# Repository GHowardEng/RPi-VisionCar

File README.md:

# RPi-VisionCar
## OpenCV vision-based maze car project

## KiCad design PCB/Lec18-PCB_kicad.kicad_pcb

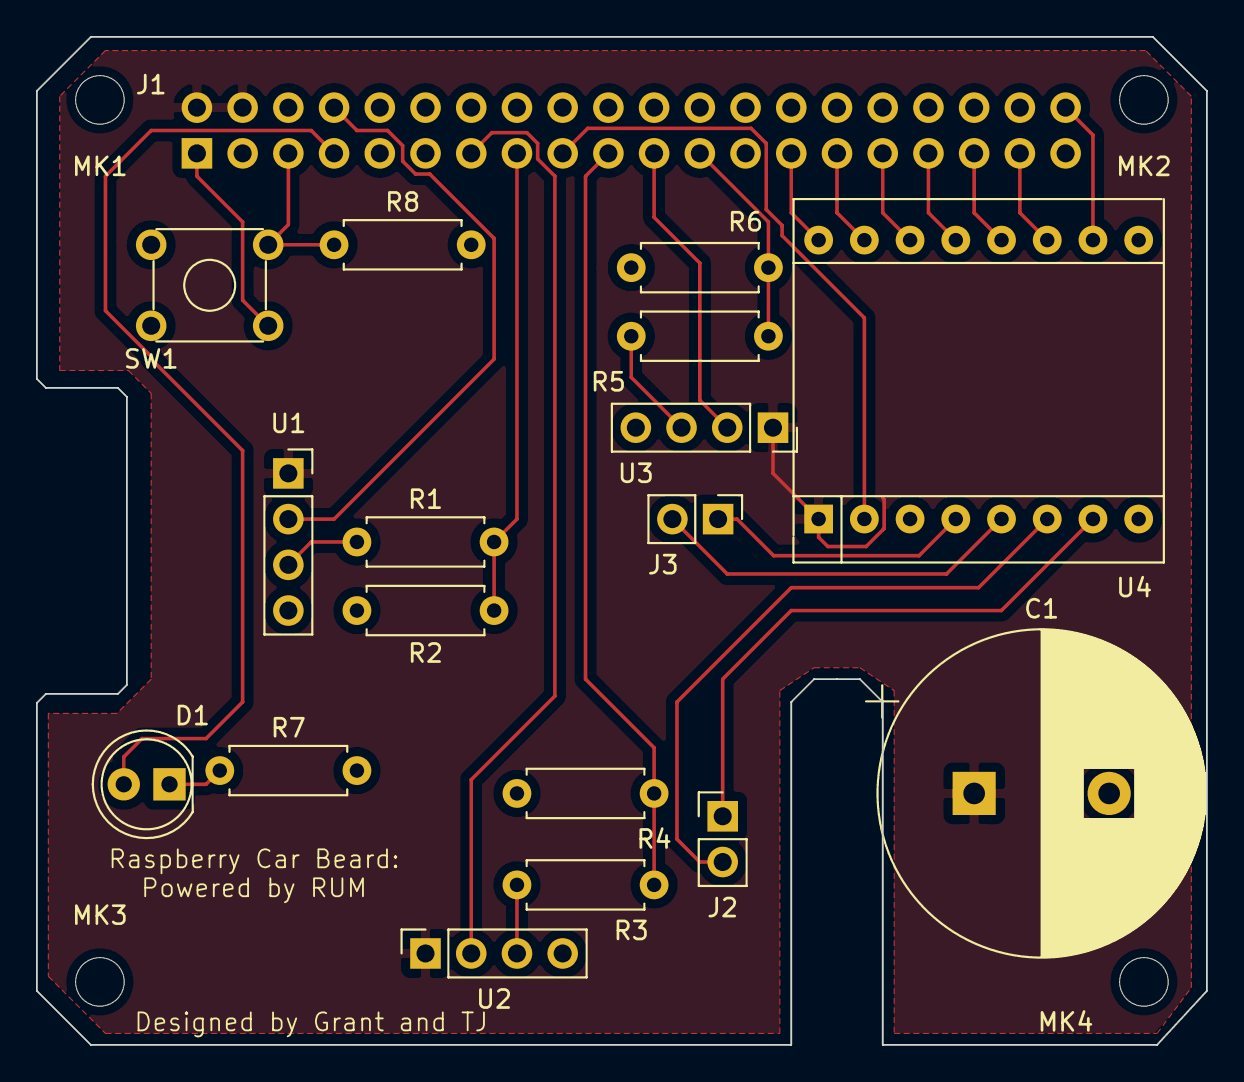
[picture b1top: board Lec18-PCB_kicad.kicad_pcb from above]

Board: 2 copper layers, 65.0 x 56.0 mm, 22 parts (1 on the bottom side), 26 nets.

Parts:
C1: CAP; CP_Radial_D18.0mm_P7.50mm
D1: LED; LED_D5.0mm
J1: Raspberry_Pi_2_3; PinSocket_2x20_P2.54mm_Vertical
J2, J3: Conn_01x02_Male; PinHeader_1x02_P2.54mm_Vertical
MK1, MK2, MK3, MK4: M2.5; MountingHole_2.7mm_M2.5
R1, R2, R3, R4, R5, R6, R7, R8: R; R_Axial_DIN0207_L6.3mm_D2.5mm_P7.62mm_Horizontal
SW1: SW_Push_Dual; SW_TH_Tactile_Omron_B3F-10xx
U1, U2, U3: HC-SR04; PinSocket_1x04_P2.54mm_Vertical
U4: TB6612FNG_BREAKOUT; SparkFun_TB6612_foot

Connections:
+3V3: J1.1, J1.17, SW1.4, U4.2
+5V: C1.1, J1.2, J1.4, U1.1, U2.1, U3.1, U4.1
A01: J3.1, U4.4
A02: J3.2, U4.5
AIN1: J1.31, U4.14
AIN2: J1.29, U4.15
B01: J2.1, U4.7
B02: J2.2, U4.6
BIN1: J1.35, U4.12
BIN2: J1.37, U4.11
GND: C1.2, J1.6, J1.9, J1.14, J1.20, J1.25, J1.30, J1.34, J1.39, R2.2, R4.2, R6.2, R7.2, R8.2, U1.4, U2.4, U3.4, U4.3, U4.8, U4.9
LED: D1.2, J1.7
unnamed: D1.1, R7.1
P1_ECHO: J1.15, R1.2, R2.1
P2_ECHO: J1.19, R3.2, R4.1
P3_ECHO: J1.23, R5.2, R6.1
PUSH_BUTTON: J1.5, R8.1, SW1.2
PWMA: J1.27, U4.16
PWMB: J1.40, U4.10
STBY: J1.33, U4.13
U1_ECHO: R1.1, U1.3
U1_TRIG: J1.8, U1.2
U2_ECHO: R3.1, U2.3
U2_TRIG: J1.13, U2.2
U3_ECHO: R5.1, U3.3
U3_TRIG: J1.21, U3.2

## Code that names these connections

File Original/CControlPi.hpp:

#pragma once
#include <string>

using namespace std;

enum TYPE { DIGITAL = 0, ANALOG, SERVO };
enum DIR { LEFT = 0, RIGHT};

#define Ai1 6
#define Ai2 5
#define PWMa 30		// Control pins for motor A

#define Bi1	19
#define Bi2 26
#define PWMb 29		// Control pins for motor B

#define STBY 13		// Motor controller standby pin

#define LED 4 		// BCM pin for PiHAT LED
#define SW	17		// BCM pin for PiHAT pushbutton

#define SERVO_MAX 2500
#define SERVO_MIN 700

enum drive_state { STOP = 0, FORWARD, REVERSE };

class CControlPi
{
private:
	int lastval[5];  ///< Stores previous button state for de-bouncing
	
public:
	CControlPi();
	int drive = STOP;
	bool get_data(int type, int channel, int &value);
	bool set_data(int type, int channel, int value);
	int get_button(int channel, int index);
	int get_analog(int channel, int &value);
	void print_menu(void);
	
	void turn(int dir);
	void forward(void);
	void reverse(void);
	void stop(void);
	void correct(int dir);
	void setSpeed(int val);
	void readInput(string input);
	
};

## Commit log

2022-01-09 Init repo with legacy files from RPi
2022-01-09 Additional project files
2022-01-09 CControlPi updates
2022-01-09 Add working CAD files
2022-01-11 New .stl files
2022-01-14 Add Pose Estimation programs and other openCV python scripts
    - Calibration, Chessboard pose, ArUco pose
2022-01-15 Update CAD assembly and components
2022-01-15 Update CAD assembly
